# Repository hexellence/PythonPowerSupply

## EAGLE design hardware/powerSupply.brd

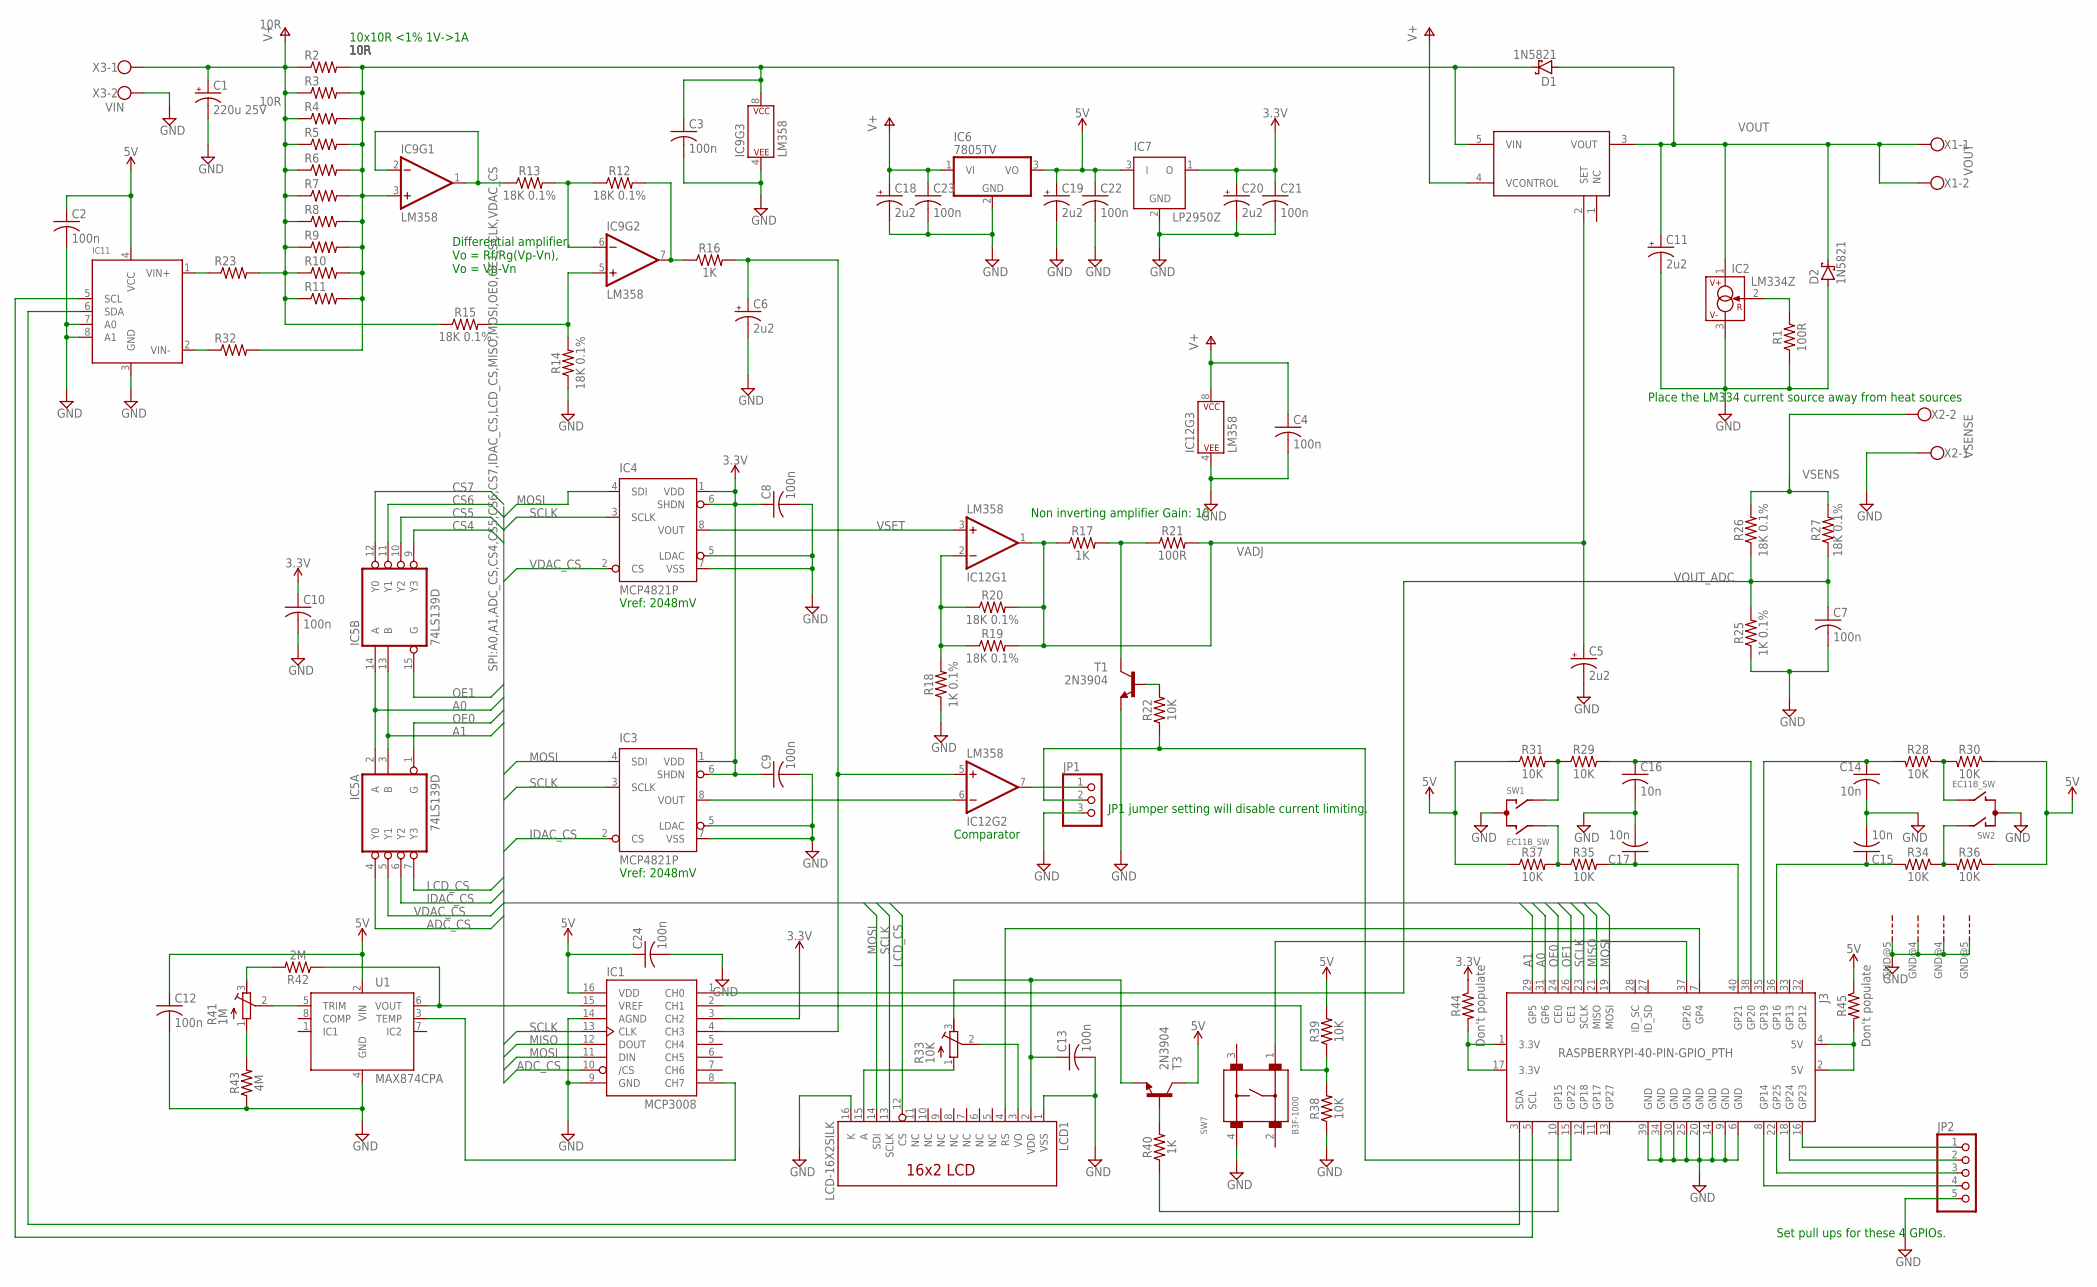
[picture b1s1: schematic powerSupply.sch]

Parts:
C1: 220u 25V; E5-6
C2, C3, C4, C7, C8, C9, C10, C12, C13, C21, C22, C23, C24: 100n; C050-024X044
C5, C6, C11, C18, C19, C20: 2u2; E2-5
C14, C15, C16, C17: 10n; C050-024X044
D1, D2: 1N5821; C4111-15
IC1: MCP3008; DIL16
IC2: LM334Z; TO92
IC3, IC4: MCP4821P; DIP08
IC5: 74LS139D; SO16
IC6: 7805TV; TO220V
IC7: LP2950Z; TO92
IC8: LT3080T; TO220-5
IC9, IC12: LM358; DIP08
IC11: INA219; SOT23-8
J3: RASPBERRYPI-40-PIN-GPIO_PTH; 2X20_SHROUDED
JP1: PINHD-1X3; 1X03
JP2: PINHD-1X5; 1X05
LCD1: LCD-16X2SILK; LCD-16X2
R1, R21: 100R; 0204/7
R2, R3, R4, R5, R6, R7, R8, R9, R10, R11, R23, R32: 10R; 0207/12
R12, R13, R14, R15, R19, R20, R26, R27: 18K 0.1%; 0204/7
R16, R17, R40: 1K; 0204/7
R18, R25: 1K 0.1%; 0204/7
R22, R28, R29, R30, R31, R34, R35, R36, R37, R38, R39: 10K; 0204/7
R33: 10K; RTRIM64W
R41: 1M; RTRIM64W
R42: 2M; 0204/7
R43: 4M; 0204/7
R44, R45: Don't populate; 0204/7
SW1, SW2: EC11B_SW; APLS_EC11B_SW
SW7: B3F-1000
T1, T3: 2N3904; TO92
U1: MAX874CPA; DIP08
X1: VOUT; W237-102
X2: VSENSE; W237-102
X3: VIN; W237-102

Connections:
0.064V@25C: IC2.2 (R), R1.2
3.3V: C8.1, C9.1, C10.1, C20.+, C21.1, IC1.3 (CH2), IC3.1 (VDD), IC3.6 (SHDN), IC4.1 (VDD), IC4.6 (SHDN), IC7.1 (O), R44.1
4.096V: IC1.15 (VREF), R42.1, U1.6 (VOUT)
5V: C2.1, C12.1, C19.+, C22.1, C24.1, IC1.16 (VDD), IC6.3 (VO), IC7.3 (I), IC11.4 (VCC), R30.1, R31.1, R36.1, R37.1, R39.2, R45.1, T3.1 (C), U1.2 (VIN)
A0: IC5.2 (A), IC5.14 (A), J3.31 (GP6)
A1: IC5.3 (B), IC5.13 (B), J3.29 (GP5)
ADC_CS: IC1.10 (/CS), IC5.4 (Y0)
ADC_IOUT: C6.+, IC1.4 (CH3), IC12.5 (+IN), R16.2
CS4: IC5.9 (Y3)
CS5: IC5.10 (Y2)
CS6: IC5.11 (Y1)
CS7: IC5.12 (Y0)
GND: C1.-, C2.2, C3.2, C4.2, C5.-, C6.-, C7.2, C8.2, C9.2, C10.2, C11.-, C12.2, C13.2, C14.2, C15.2, C16.2, C17.2, C18.-, C19.-, C20.-, C21.2, C22.2, C23.2, C24.2, D2.A, IC1.9 (GND), IC1.14 (AGND), IC2.3 (V-), IC3.5 (LDAC), IC3.7 (VSS), IC4.5 (LDAC), IC4.7 (VSS), IC5.8 (GND), IC6.2 (GND), IC7.2 (GND), IC9.4 (P$V-), IC11.3 (GND), IC11.7 (A0), IC11.8 (A1), IC12.4 (P$V-), J3.6 (GND), J3.9 (GND), J3.14 (GND), J3.20 (GND), J3.25 (GND), J3.30 (GND), J3.34 (GND), J3.39 (GND), JP1.3, JP2.5, LCD1.1 (VSS), LCD1.16 (K), R1.1, R14.1, R18.1, R25.1, R38.1, R43.1, SW1.GND@4 (G), SW1.GND@5 (G), SW1.P$3 (C), SW2.GND@4 (G), SW2.GND@5 (G), SW2.P$3 (C), SW7.4, T1.3 (E), U1.4 (GND), X2.1, X3.2
IDAC_CS: IC3.2 (CS), IC5.6 (Y2)
LCD_CS: IC5.7 (Y3), LCD1.12 (CS)
MISO: IC1.12 (DOUT), J3.21 (MISO)
MOSI: IC1.11 (DIN), IC3.4 (SDI), IC4.4 (SDI), J3.19 (MOSI), LCD1.14 (SDI)
unnamed: IC3.8 (VOUT), IC12.6 (-IN)
unnamed: IC1.2 (CH1), R38.2, R39.1
unnamed: LCD1.3 (VO), R33.2 (S)
unnamed: IC11.1 (VIN+), R23.1
unnamed: IC1.8 (CH7), U1.3 (TEMP)
unnamed: IC9.1 (OUT), IC9.2 (-IN), R13.1
unnamed: IC9.6 (-IN), R12.1, R13.2
unnamed: R17.2, R21.1, T1.1 (C)
unnamed: IC9.5 (+IN), R14.2, R15.2
unnamed: C4.1, IC12.8 (P$V+)
unnamed: IC9.7 (OUT), R12.2, R16.1
unnamed: R22.2, T1.2 (B)
unnamed: IC12.2 (-IN), R18.2, R19.1, R20.1
unnamed: IC12.7 (OUT), JP1.1
unnamed: LCD1.15 (A), R33.1 (A)
unnamed: IC11.2 (VIN-), R32.1
unnamed: J3.15 (GP22), JP1.2, R22.1
unnamed: J3.7 (GP4), LCD1.4 (RS)
unnamed: R28.1, R30.2, SW2.P$2 (B)
unnamed: C14.1, J3.35 (GP19), R28.2
unnamed: C15.1, J3.36 (GP16), R34.2
unnamed: R34.1, R36.2, SW2.P$1 (A)
unnamed: C16.1, J3.38 (GP20), R29.2
unnamed: C17.1, J3.40 (GP21), R35.2
unnamed: R29.1, R31.2, SW1.P$1 (A)
unnamed: R35.1, R37.2, SW1.P$2 (B)
unnamed: J3.16 (GP23), JP2.1
unnamed: J3.18 (GP24), JP2.2
unnamed: J3.22 (GP25), JP2.3
unnamed: J3.8 (GP14), JP2.4
unnamed: IC11.6 (SDA), J3.3 (SDA)
unnamed: IC11.5 (SCL), J3.5 (SCL)
unnamed: J3.37 (GP26), SW7.1
unnamed: R40.2, T3.2 (B)
unnamed: C13.1, LCD1.2 (VDD), R33.3 (E), T3.3 (E)
unnamed: J3.10 (GP15), R40.1
unnamed: R41.2 (S), U1.5 (TRIM)
unnamed: R41.3 (E), R42.2
unnamed: J3.1 (3.3V), J3.17 (3.3V), R44.2
unnamed: R41.1 (A), R43.2
unnamed: J3.2 (5V), J3.4 (5V), R45.2
OE0: IC5.1 (G), J3.24 (CE0)
OE1: IC5.15 (G), J3.26 (CE1)
SCLK: IC1.13 (CLK), IC3.3 (SCLK), IC4.3 (SCLK), J3.23 (SCLK), LCD1.13 (SCLK)
VADJ: C5.+, IC8.2 (SET), IC12.1 (OUT), R17.1, R19.2, R20.2, R21.2
VCC: IC5.16 (VCC)
VDAC_CS: IC4.2 (CS), IC5.5 (Y1)
VOUT: C11.+, D1.A, D2.C, IC2.1 (V+), IC8.3 (VOUT), X1.1, X1.2
VOUT_ADC: C7.1, IC1.1 (CH0), R25.2, R26.1, R27.1
VR: C3.1, D1.C, IC8.5 (VIN), IC9.3 (+IN), IC9.8 (P$V+), R2.2, R3.2, R4.2, R5.2, R6.2, R7.2, R8.2, R9.2, R10.2, R11.2, R32.2
VSENS: R26.2, R27.2, X2.2
VSET: IC4.8 (VOUT), IC12.3 (+IN)

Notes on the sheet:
10x10R <1% 1V->1A
JP1 jumper setting will disable current limiting.
Set pull ups for these 4 GPIOs.
Place the LM334 current source away from heat sources
Non inverting amplifier Gain: 10
Vref: 2048mV
Comparator
Differential amplifier, Vo = Rf/Rg(Vp-Vn), Vo = Vp-Vn

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
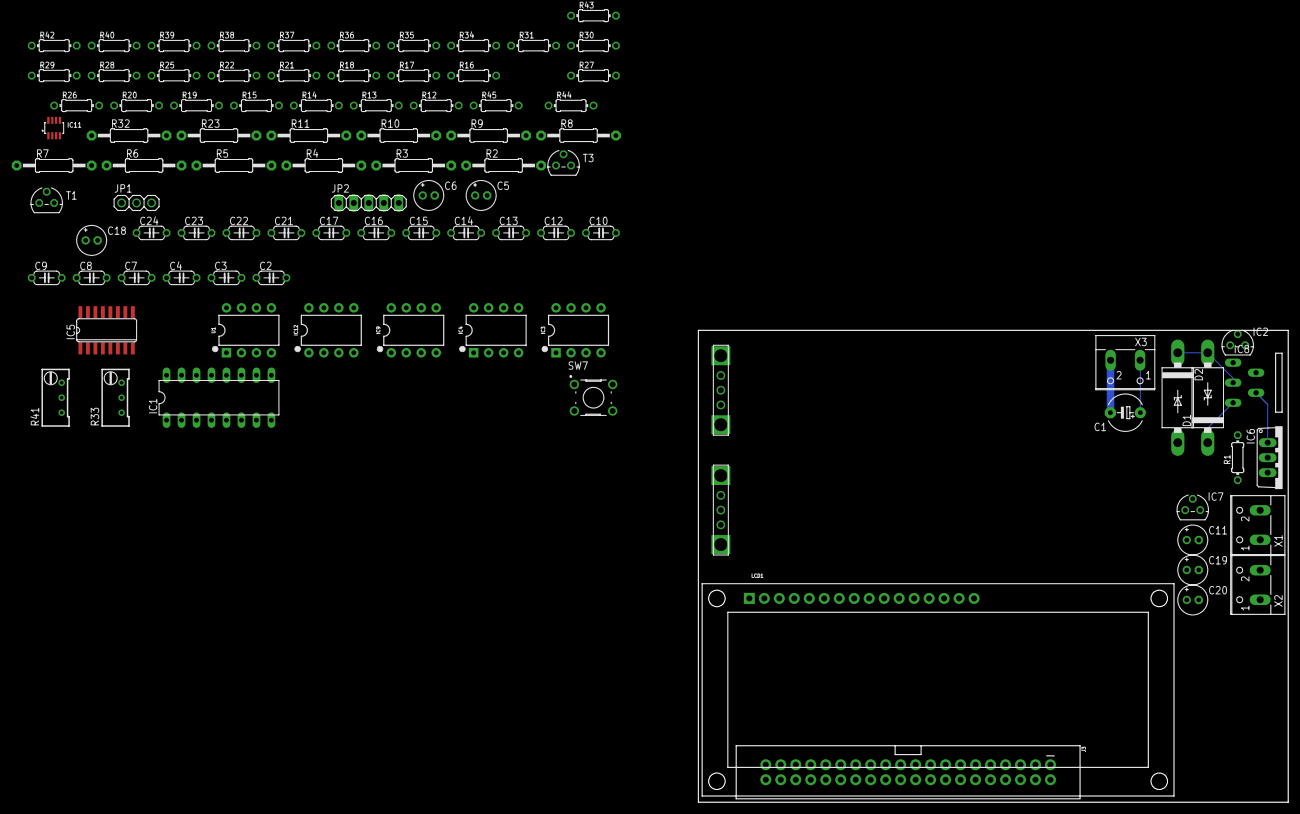
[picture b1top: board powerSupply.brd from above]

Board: 2 copper layers, 100.0 x 80.0 mm, 94 parts (0 on the bottom side), 66 nets.

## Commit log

2019-12-15 added length parameter to lcd writeloc command
2019-12-15 corrected unit section
2019-12-15 similar LCD screen implemented
2019-12-20 removed extraneous stuff
2019-12-22 very pleased with this. pigpio is used. so there is a very big dependency to an external code
2019-12-22 this is better than the previous. timing window is implemented
2019-12-22 added the trimmers. and LCD switch tranny
2020-01-29 Works fine. sometimes knobs are acting but now I'll fix the hardware
2020-02-05 mqtt support

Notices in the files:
parts and their libraries:
SparkFun-IC-Amplifiers: Licensing: Creative Commons ShareAlike 4.0 International - https://creativecommons.org/licenses/by-sa/4.0
